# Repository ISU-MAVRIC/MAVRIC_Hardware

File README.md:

MAVRIC_Hardware
===============

Hardware design files for MAVRIC

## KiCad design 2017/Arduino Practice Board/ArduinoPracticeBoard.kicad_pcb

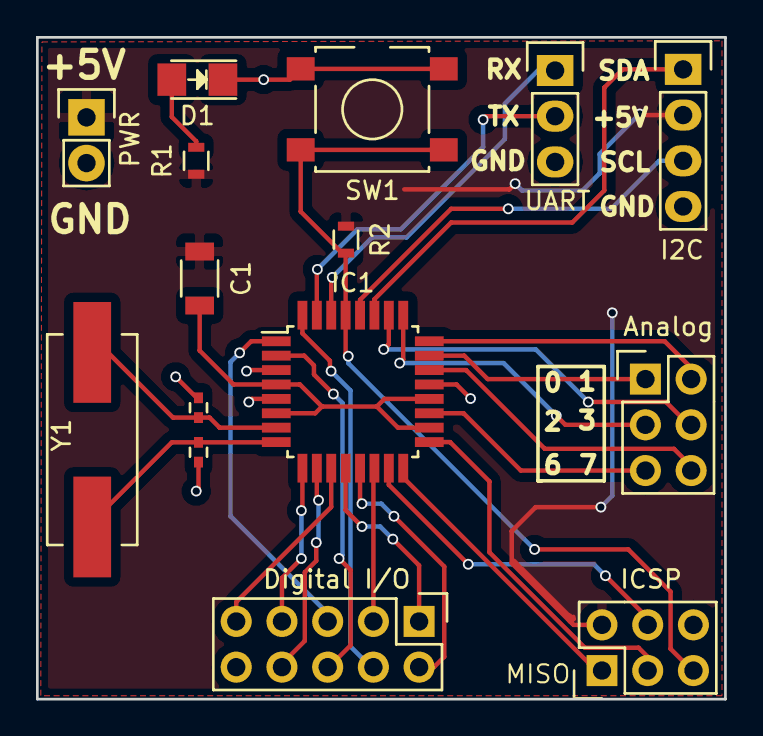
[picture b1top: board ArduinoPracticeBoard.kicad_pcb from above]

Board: 2 copper layers, 38.2 x 36.8 mm, 15 parts (0 on the bottom side), 29 nets.

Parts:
Analog: Analog; Pin_Header_Straight_2x03
C1: 10u; C_1206
CXtalIn1: 18pf; C_0402
CXtalout1: 18pf; C_0402
D1: LED; LED_1206
Digital I/O: Digital; Pin_Header_Straight_2x05
I2C: I2C; Pin_Header_Straight_1x04
IC1: ATMEGA328-A; TQFP-32_7x7mm_Pitch0.8mm
ICSP: ICSP; Pin_Header_Straight_2x03
PWR: Power; Pin_Header_Straight_1x02
R1: <10k; R_0603
R2: 10k; R_0603
SW1: SPST; SW_SPST_B3S-1100
UART: UART; Pin_Header_Straight_1x03
Y1: 16MHz; Crystal_HC49-SD_SMD

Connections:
+5V: C1.1, I2C.2, ICSP.2, PWR.1, R1.1, R2.1
/ADC0: Analog.1, IC1.23
/ADC1: Analog.2, IC1.24
/ADC2: Analog.3, IC1.25
/ADC3: Analog.4, IC1.26
/ADC6: Analog.5, IC1.19
/ADC7: Analog.6, IC1.22
/MISO: IC1.16, ICSP.1
/MOSI: IC1.15, ICSP.4
/OSC1: CXtalIn1.2, IC1.7, Y1.2
/OSC2: CXtalout1.2, IC1.8, Y1.1
/PB0: Digital I/O.1, IC1.12
/PB1: Digital I/O.2, IC1.13
/PB2: Digital I/O.3, IC1.14
/PD2: Digital I/O.4, IC1.32
/PD3: Digital I/O.5, IC1.1
/PD4: Digital I/O.6, IC1.2
/PD5: Digital I/O.7, IC1.9
/PD6: Digital I/O.8, IC1.10
/PD7: Digital I/O.9, IC1.11
/RST: IC1.29, ICSP.5, R2.2, SW1.1
/RX: IC1.30, UART.1
/SCK: IC1.17, ICSP.3
/SCL: I2C.3, IC1.28
/SDA: I2C.1, IC1.27
/TX: IC1.31, UART.2
GND: CXtalIn1.1, CXtalout1.1, D1.1, Digital I/O.10, I2C.4, IC1.3, IC1.5, IC1.21, ICSP.6, PWR.2, SW1.2, UART.3
unnamed: C1.2, IC1.4, IC1.6, IC1.18, IC1.20
unnamed: D1.2, R1.2

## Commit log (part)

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2013-11-02 Start over
2013-11-02 File Upload
2013-11-03 Starting New Suspension Geometry
2013-11-04 New King Joint, Geometry Planning
2013-11-05 New parts for the updated Suspension Design
2013-11-06 Connected rocker and bogie
    Misc changes
2013-11-08 Add mount holes to joints
    Add rough components for diff bar
2013-11-09 Add differential bar
2013-11-12 Lightening Components and Misc. Stress testing
2013-11-13 Weight reduction
2013-11-13 Weight reduction and chassis
2013-11-13 Build chassis
2013-11-14 Temp diff fitting
2013-11-14 Differential mates
2013-11-14 Starting a secondary chassis design
2013-11-14 Updated wheel fixturing setup
2013-11-14 Uploaded soil sample tool parts
2013-11-15 Adding Mastercam files for Soil Sample Tool
2013-11-19 Updated mastercam for soil sample
2013-11-25 Mastercam for the King Joint
2013-11-25 Mastercam for King Joint and Updated Gearbox Components
2013-11-25 Change output face thickness
2013-11-25 Update gearbox cover
2013-11-25 Finished Mastercam for King Joint
2013-11-25 Add motor driver and mount to steering assembly
2013-11-25 Change box chassis to billet side rails
2013-11-25 Rocker Rear Leg CAM and Bogie-Rocker Joint CAM
2013-11-25 Updated tools in Mastercam files/ added new Mastercam files
2013-11-26 Add gear to servo axle
2013-11-26 Mastercam Files and Fixturing Setups
2013-11-26 Updated Tooling in Mastercam Files
2013-11-26 Camera assembly
2013-11-26 Modify suspension assembly to mate with new chassis
2013-11-26 Fix solidworks fubar
2013-11-26 Add antennas to overall assembly
2013-11-26 Lightening diff bar
2013-11-26 Mount batteries in overall assembly
2013-11-26 Mastercam for Rocker Leg and Bogie Leg
2013-12-03 Crossbar weight reduction
2013-12-04 Side Rail weight reduction
2013-12-04 Reduce crossbar flange thickness
2013-12-04 Reduce Front Bar flange thickness
2013-12-04 Update camera assembly
    Fix FCB EX1020 hole patterns.
    Add camera control board.
2013-12-04 Add concept arm
2013-12-04 Fix intercut spacing on Front Bar
2013-12-04 Update global assembly
2013-12-04 Concept payload components
2013-12-05 Added Payload System into Assembly
2013-12-05 Create camera mount system
2013-12-05 Mount camera system
2013-12-05 Remove study files to save space
2013-12-05 New stuff
2013-12-05 Added Photo
2013-12-06 Uploading MAVRIC Poster
2013-12-06 Updated MAVRIC Poster
2013-12-06 Changed text in MAVRIC Poster
2013-12-09 Updated Ordering Forms
2013-12-09 Updated Mastercam for Rocker to Bogie Joint
2013-12-10 Fixed ALL Mastercam Programs
2013-12-10 Moved Reports to Dropbox
2013-12-11 Added New mastercam files for Bogie Joint / Misc. New fixturing parts
2013-12-13 Updated Tools in Mastercam files / Added Wheel Joint Mastercam
2013-12-29 Updated Mastercam Files
2013-12-29 Updated Mastercam for Wheel Joint
2013-12-30 upper and lower arm (weight down)
    took a good amount of the weight down on both pieces
2014-01-03 Migrating Files From CNC Machine
2014-01-06 Add missing machining relief fillet
2014-01-06 Propagate changes to assemblies
2014-01-06 Update steering plate thickness
    Increase tearout distance in drop plates.
    Increase thickness of steering plate to fit
2014-01-06 Add fabrication drawings for drop plates
2014-01-06 Upper and lower
2014-01-06 Update side rail height
    Stock problem, need to reduce height to less than 4"
2014-01-06 mastercam
2014-01-08 Updated Mastercam for King Joint and Chassis
2014-01-08 Deleted unneeded Chassis Parts/Added Mastercam for Cross Bar
2014-01-08 Reduce crossbar thickness
    Neck down the middle of the crossbar to fix intersection with top cover
    and battery assembly introduced in
    23dd18734d2d7d3443c654bee0143aaf699bfa82
2014-01-09 Updated Mastercam for Cross Bar
2014-01-09 Update bogie joint to as built
2014-01-09 soil sample tool Mastercam
2014-01-09 Added And Updated Mastercam Files
2014-01-09 Add turn table
2014-01-10 Add turn table to arm assembly as placeholder
2014-01-10 Added New Wheel Design
2014-01-10 Updated Diff Bar Design for Fabrication
2014-01-11 Updated Chassis Front Bar CAD and CAM and the main Assembly
2014-01-15 Uploaded .PDF of Waterjet cutout
2014-01-15 Update drive gearbox to correct hole pattern and length
2014-01-21 New drawings
2014-01-21 Apparently this needed to be rebuilt
2014-01-26 Deleted Unneeded Files and Added Cross Bar CAM
2014-01-29 arm assembly 2014
    this is the new raw design of the new arm, there are still some
    constrains and some errors, but it's starting to look useful
2014-01-29 arm assembly
    just found a better position for the bracket in the lower arm, there are
    3 small interferences, easy to fix.
2014-02-04 Added battery bracket
2014-02-06 arm with lots of upgrades
    this new arm has a bracket for the actuator, and all the positions of
    the joints have been tested for its maximum efficiency. The base of the
    arm counts with a set of gears and a motor to spin the the base.
2014-02-06 Updated End Effector
2014-02-07 added L bracket
2014-02-07 added and updated end effector parts
2014-02-07 Added Soil Sample tool (Bucket)
2014-02-10 Fixed Main Assembly and added a few Rendered Photos
2014-02-11 arm ready for design review
    the arm has the gears selected for the base, there's also a base plate
    I've made to attach to the chassis. I've also taken down a lot of
    weight. This thing looks fantastic.
2014-02-12 Added general design and servo part
2014-02-12 Updated Chassis and End Effector
2014-02-12 Added servo assembly and parts
2014-02-14 added small gear assembly and parts
2014-02-18 arm weight reduction
    started to do weight reduction, many of the tap-holes are already made,
    looking pretty good.
2014-02-19 Bottom Chassis cover
    Initial upload, in process of completion
2014-02-19 Added a lot of servo work
2014-02-20 Differential Bar CAM and Camera Fixture Work
2014-02-21 almost fixed a new location for the motor drive
    if you open the arm weight reduc file, you can see a mount where the
    motor is resting. I am still trying to find a better spot, I will get it
    soon.
2014-02-22 created the end effector assembly for review
2014-02-25 mounts for the cross-bar, good motor location
    finally came up with a good location for the motor, started working on
    some brackets for the cross-bar
2014-02-26 end effector assembly work added
2014-02-27 added work on servo bracket
2014-02-27 added bracket work
2014-02-27 changed the second bracket
2014-02-28 add version 1 of end effector assembly + brackets
2014-03-03 Added slots for grooves for bottom track
2014-03-04 Diff Yoke Updated
2014-03-04 Changed pattern on bottom cover to fit into bottom support
2014-03-04 Fixed dimensions
2014-03-04 Fixed more dimensions
2014-03-06 Added bracket to connect servo 1 and 2
2014-03-06 fixed bracket
2014-03-06 Added midterm design review
2014-03-07 added stress test to end effector
2014-03-07 New ppt file and rendering for chassis bottom cover
2014-03-08 Work on photo render for powerpoint
2014-03-08 Added end effector power point portion
2014-03-08 Updates and made top front cover from copy of rear top
2014-03-08 added corrected low torque servo assembly
2014-03-08 Fixed hole locations to fit chassis assembly
2014-03-08 updated bracket and powerpoint
    Put a chamfer on the bracket and did more of the powerpoint
2014-03-11 added updated gearbox brackets
2014-03-12 GEARS FINALLY WORK
    After a very intense period of crying and torture, I've been able to
    find a good solution for the spinning mechanism of the arm. Almost all
    of it could be machined right now. Last thing to work on is the
    attachments to the cross-member.
2014-03-12 Camera Mount Mastercam
2014-03-13 added work on the end effector brackets
2014-03-13 Camera Mount Fixture Mastercam
2014-03-13 added bracket for servo 2 to servo 3
2014-03-13 Diff Bar Render
2014-03-13 Battery Bracket Render
2014-03-13 Chassis assembly render and Powerpoint
2014-03-13 added servo bracket (needs revision and testing)
2014-03-14 arm updates and power point portion
    Here's some new things on the arm, I' still deciding where to put the
    cross member mounts, but I'll get there today. Here's also my portion of
    the pp.
2014-03-21 Modified Chassis Covers and Upper Arm
2014-03-21 Updated Arm Components
2014-03-22 Updated Material Thickness on Arm / Added Mastercam for Base Plate
2014-03-22 Deleted Study Files
2014-03-24 modified arm with correct mounts
    Did some modifications to the arm to work properly and also changed a
    bit the mounts to accommodate the new size of it.
2014-03-27 finished base bracket design
2014-04-01 Organized
    It was messy, fixed also update chassis top right cover panel
2014-04-03 work on weight reduction of bracket
2014-04-03 weight reduction of bracket 2-3 "completed"
2014-04-03 Upper Arm Cam
2014-04-03 Molds done
2014-04-08 weight recud end effector bracket corrected
    just some minor adjustments
2014-04-08 weight reduc end effector bracket recorrected
    some weight reduction was made and also some stress tests to make sure
    it worked properly.
2014-04-10 changes to brackets
2014-04-10 big gear hub radius fixed
2014-04-10 finished bracket 2-3
2014-04-11 weight reduction continued
2014-04-11 (finally) finished end effector model
2014-04-11 Added fillets
2014-04-11 Reduce weight
2014-04-17 new chassis mounts
    did some major cleaning on the folder, created the brackets to hold the
    arm to the chassis
2014-04-26 Updated MAVRIC Assembly with new subsystems
2014-04-29 Set up Final Report folder
2014-04-29 Added MAVRIC final report Master
2014-04-29 added final report section for end effector
2014-05-01 Added Base Station Control section
    Condensed explanation of the rover's base station control software.
2014-05-01 Updated Final Report.... again
2014-05-02 Chassis report (needs pictures)
2015-01-25 MAVRIC KiCad Component Library Created
    Will contain all custom parts for the MAVRIC PCBs
2015-01-25 Added AZ34063UMTR-G1 to KiCad Lib
    Voltage regulator
2015-01-25 Added gitignore
2015-01-25 Added 485 and Battery connectors
    Still need footprints, but that's to be decided
2015-01-26 Added AP65552SP-13 Regulator
    Higher current regulator for servos on arm board
2015-01-26 Added AOZ1280CI Regulator
    Lower current for less intensive use cases (micro)
2015-01-26 Added lower cost 485 transceiver SN75176BDR
2015-01-26 Renamed incorrectly named STM32F401
2015-01-26 Added SyRen serial connector
2015-01-26 Added raspberry pi power connector
2015-01-28 Added 74LVCH244APW buffer
    Planned use for long PWM lines coming from arm board
2015-01-28 Added connector for linear actuator feedback
2015-01-28 Added SWD Connector
2015-01-29 added MAVRIC footprint library
2015-01-30 added footprints for MicroSMP diode and inductor
    first time footprinting, may be some mistakes
2015-01-30 Fixed pins numbered 0, added wire pad
    Wire pad for power on arm board but will be replaced
2015-01-31 changed package pad of AP regulator to pin 9
    matches the footprint now
2015-02-07 Added ZXCT1107 Current Sense Part
    Also added .db files to gitignore because thumbs.db
2015-02-08 Fixed STM32 Part
    Deleted VSS and VDD that didn't exist. Added PD2
2015-02-18 Add ground to 485, add 232 header
2015-03-05 Add plated mounting hole
2015-03-06 Add Molex RJ45 Jack footprint
    ISU-MAVRIC/MAVRIC_WheelPod#5
2015-03-07 Add 6 pad solder pad footprint
2015-03-08 Add MAVRIC logo and new breakaway headers
    Resolves ISU-MAVRIC/MAVRIC_Arm#38
2015-03-08 Fix pad numbers on 1x6_Breakaway_Header
2016-09-24 Add AP6503 Regulator
    New 5v 3A regulator
2016-10-01 Rearranged folder
2016-11-04 Add Arduino Practice Board
    Arduino board to practice soldering as a fun project to newbs. Contains
    ordering information and reciepts.
2016-11-07 Init commit of Motherboard
    New motherboard using MSP432 as communication and periphrial controller
2017-01-06 Motherboard - Correct PINOUT to match TI pinmux, add HF X, create PCIe_36 footprint, add temperature sensor, create and assign netlist, BOM
2017-01-08 Start layout of motherboard
2017-01-10 Finish Mobo v1.0
    Add XT60 power conector, add mounting holes, finish layout of
    Motherboard v1.0
2017-01-10 Create and Finish ControlCard v1.0
    The control board has 16 PWM outputs and 4 ADC inputs intended or
    feedback
2017-01-10 Add new connectors
2017-02-14 This is asummary
    This is a description
2017-02-15 Soil Science board initial commit
    This is the science board without the edge card slot, motor controller,
    laser power supply, or any additional features to show up in the final
    design.
